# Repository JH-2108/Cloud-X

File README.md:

# Cloud-X
An educational model rocketry project exploring aerospace engineering, embedded programming and systems, electronics design and flight-data analysis

# Overview
This project explores the development of a model rocket and an accompanying STM32 based avionics data logging system. 

The electronics project focuses on collecting and recording sensor measurements, allowing data to be studied and visualized during engineering expreiments. 

# Objectives
- Explore aerospace engineering and model rocketry.
- Design a custom PCB using KiCAD
- Develop embedded firmware for an STM32 microcontroller
- Integrate motion and atmospheric pressure sensors
- Implement microSD data storage
- Analyze sensor measurements and visualize recorded data.
- Document the engineering and development process.

# Electronics
The avionics electronics design uses the following main components

|Component|Purpose|
|---|---|
|STM32F7SSRET6|Main microcontroller | 
| ICM-45686 | Motion sensin |
| BMP580 | Atmospheric pressure measurement | 
| HRS DM3D SF | microSD card interface | 
| USB type C | Programming and data transfer | 
| AP2112K-3.3 | Voltage regulation | 
| USBLC6-2SC6 | USB ESD protection | 

# PCB designing 
The custom PCB is designed using KiCAD 
The electronics documentation covers: 
- Schematic design
- PCB layout
- Component selection
- power-management review
- sensor integration
- firmware development
- design rule verification

# Firmware
Firmware development focuses on: 
- STM32 intialization
- Sensor communication
- Sensor data acquisition
- microSD data recording
- USB communication
- Diagnostic information

# Payload Ejection Plan
A motor engine would be used to propel the rocket upwards, upon hitting the apogee, the PCB would send out a tiny electrical signal to the e-matches, allowing the nose cone to release, the nose cone and the rest of the rocket body is connected through a shock cord, where the parachute would be opened closer to the nose cone instead, giving a large space for the flight controller to be released. This flight controller will  then measure altitude, atmospheric pressure, acceleration, and more, all of which is written onto an microSD card within the rocket flight controller itself. 

# Development tools 
- KiCAD: PCB and schematic design
- STM32CubeIDE: Embedded development
- OpenRocket software: Rocket designing 

# Safety 
This repository documents an educational aerospace engineering project. Any physical rocketry activities must follow applicable laws, recognized model rocketry safety standards and qualified adult supervision. 

The electronics documentation is **NOT** an instruction manual for constructing or operation propulsion or pyrotechnic systems. 

# BOM 
|Part                                                                                                                    |Type      |Quantity|Unit price (USD)|Line total (USD)|Link                                                                                                                                                                                                                                                                                                              |Vendor         |Funding|Notes                                                                      |
|------------------------------------------------------------------------------------------------------------------------|----------|--------|----------------|----------------|------------------------------------------------------------------------------------------------------------------------------------------------------------------------------------------------------------------------------------------------------------------------------------------------------------------|---------------|-------|---------------------------------------------------------------------------|
|STM32F722RET6                                                                                                           |Part      |1       |11.30           |11.30           |https://www.lcsc.com/product-detail/C118207.html?s_z=n_q_STM32F722RET6                                                                                                                                                                                                                                            |LCSC           |Grant  |Main microcontroller chip                                                  |
|ICM-45686                                                                                                               |Part      |1       |10.31           |10.31           |https://www.lcsc.com/product-detail/C22459454.html?s_z=n_q_ICM-45686                                                                                                                                                                                                                                              |LCSC           |Grant  |Motion sensor data acquisition                                             |
|BMP580                                                                                                                  |Part      |1       |1.21            |1.21            |https://www.lcsc.com/product-detail/C22391138.html?s_z=n_q_BMP580                                                                                                                                                                                                                                                 |LCSC           |Grant  |Atmospheric pressure measurement                                           |
|USB Type-C 16P SMT                                                                                                      |Part      |1       |0.60            |0.60            |https://www.lcsc.com/product-detail/USB-Connectors_hanxia-HX-TYPE-C-16P-SMT-J2-0_C42453849.html                                                                                                                                                                                                                   |LCSC           |Grant  |Programming and data transfer                                              |
|4.7kΩ resistor                                                                                                          |Part      |1       |0.32            |0.32            |https://www.lcsc.com/product-detail/C99782.html                                                                                                                                                                                                                                                                   |LCSC           |Grant  |I2C communication                                                          |
|ST USBLC6-2SC6                                                                                                          |Part      |1       |0.82            |0.82            |https://www.lcsc.com/product-detail/esd-and-surge-protection-tvs-esd_stmicroelectronics-usblc6-2sc6_C7519.html                                                                                                                                                                                                    |LCSC           |Grant  |ESD protection                                                             |
|SMD tactile push button, 4 pins                                                                                         |Part      |1       |0.50            |0.50            |https://www.lcsc.com/product-detail/C49234134.html?s_z=n_q_l_tactile%2520switch%2520SMD                                                                                                                                                                                                                           |LCSC           |Grant  |Reset and BOOT button                                                      |
|HONGLITRONIC PSC-1608U52GC-G4                                                                                           |Part      |1       |0.74            |0.74            |https://www.lcsc.com/product-detail/C22371297.html?s_z=n_q_0603%2520LED%2520green                                                                                                                                                                                                                                 |LCSC           |Grant  |Status LED                                                                 |
|Samsung Electro-Mechanics CL10B104KB8NNNC                                                                               |Part      |1       |0.72            |0.72            |https://www.lcsc.com/product-detail/C1591.html?s_z=n_q_t_100nf%25200603%2520capacitor                                                                                                                                                                                                                             |LCSC           |Grant  |Decoupling capacitors                                                      |
|Samsung Electro-Mechanics CL10A106KP8NNNC                                                                               |Part      |1       |0.41            |0.41            |https://www.lcsc.com/product-detail/C19702.html?s_z=n_q_t_10uF%25200603%2520capacitors                                                                                                                                                                                                                            |LCSC           |Grant  |Bulk capacitor                                                             |
|2.54mm, 1×04 pin header                                                                                                 |Part      |1       |1.03            |1.03            |https://shopee.com.my/Straight-Pin-Header-MALE-Single-Double-Row-2p-3p-4p-10p-40p-2.54mm-Pitch-i.678234279.17653071533?extraParams=%7B%22display_model_id%22%3A58675164377%2C%22model_selection_logic%22%3A2%7D&image_ids=my-11134207-7r990-ly9mj2d9bfqhc3                                                        |Shopee Malaysia|Grant  |debugging                                                                  |
|HRS DM3D-SF                                                                                                             |Part      |1       |1.60            |1.60            |https://www.lcsc.com/product-detail/C719027.html                                                                                                                                                                                                                                                                  |LCSC           |Grant  |MicroSD card holder                                                        |
|DIODES AP2112K-3.3TRG1                                                                                                  |Part      |1       |0.92            |0.92            |https://www.lcsc.com/product-detail/C51118.html?s_z=n_q_%2520C51118&globalKeyword=%2520C51118                                                                                                                                                                                                                     |LCSC           |Grant  |converts raw power input to save voltage level                             |
|DIODES B130-13-F                                                                                                        |Part      |1       |0.46            |0.46            |https://www.lcsc.com/product-detail/C134423.html                                                                                                                                                                                                                                                                  |LCSC           |Grant  |Protects the circuit if battery is placed incorrectly                      |
|UNI-ROYAL 0603WAF5101T5E                                                                                                |Part      |1       |0.16            |0.16            |https://www.lcsc.com/product-detail/C23186.html?s_z=n_q_C23186&globalKeyword=C23186                                                                                                                                                                                                                               |LCSC           |Grant  |tie CC1 and CC2 to GND                                                     |
|AOS AO3400A                                                                                                             |Part      |1       |0.45            |0.45            |https://www.lcsc.com/product-detail/C20917.html?s_z=n_q_C20917&globalKeyword=C20917                                                                                                                                                                                                                               |LCSC           |Grant  |Ignites parachutes when MCU detects apogee                                 |
|UNI-ROYAL 0603WAF1002T5E                                                                                                |Part      |1       |0.22            |0.22            |https://www.lcsc.com/product-detail/C25804.html?s_z=n_q_C25804&globalKeyword=C25804                                                                                                                                                                                                                               |LCSC           |Grant  |Manages boot configuration, ensures clean SD logging, and measures battery.|
|PCB manufacturing                                                                                                       |PCB       |1       |15.00           |15.00           |https://jlcpcb.com                                                                                                                                                                                                                                                                                                |jlcpcb         |Grant  |Rocket flight controller PCB manufacturing                                 |
|Print Legion                                                                                                            |3D printed|1       |30.00           |30.00           |https://printlegion.hackclub.com                                                                                                                                                                                                                                                                                  |print legion   |Grant  |Rocket body                                                                |
|GNB LiHV 2S 7.6V 1100mAh 60C XT30 LiPo Battery Long Range                                                               |Part      |1       |12.00           |12.00           |https://epicfpv.ca/products/gnb-lihv-2s-7-6v-1100mah-60c-xt30-lipo-battery-long-range-1?variant=60800320405790&country=MY&currency=MYR&utm_medium=product_sync&utm_source=google&utm_content=sag_organic&utm_campaign=sag_organic&srsltid=AYCX9vIx-3YrB9azhgDblcEGwU8ssDDiMy9BJdyDTWHyMrJqba1CQkDj8P8             |epicFPV        |Grant  |Battery for electronics and e-matches                                      |
|For Amass XT30PW Male For PCB Board Plug Banana Golden XT30 Connector Black 3.6mm 90 Degrees Right Angle XT30PW-M36 5NRT|Part      |1       |4.50            |4.50            |https://shopee.com.my/For-Amass-XT30PW-Male-For-PCB-Board-Plug-Banana-Golden-XT30-Connector-Black-3.6mm-90-Degrees-Right-Angle-XT30PW-M36-5NRT-i.348385455.53262738873?extraParams=%7B%22display_model_id%22%3A416107095660%2C%22model_selection_logic%22%3A3%7D&image_ids=sg-11134201-823p2-mp3yeoidr56oc4       |Shopee Malaysia|Grant  |Battery connector                                                          |
|Pyro screw terminals                                                                                                    |Part      |2       |1.00            |2.00            |https://shopee.com.my/2P-3P-4P-5P-6P-7P-8P-9P-10P-Pitch-2.54mm-3.81mm-5.00mm-5.08mm-Terminal-Block-Connector-PCB-DIY-Wire-Cable-KF128-i.90748406.20850140188?extraParams=%7B%22display_model_id%22%3A213007401440%2C%22model_selection_logic%22%3A3%7D&image_ids=my-11134207-7r98y-lwi43m3xsdwqa6                 |Shopee Malaysia|Grant  |Pyro e-matches ejector                                                     |
|E-matches for pyro system                                                                                               |Part      |1       |30.00           |30.00           |https://shopee.com.my/Electric-Ignitor-1m-2m-3m-E-Match-Talon-Firing-System-Rocket-Feux-D'artific-Fuse-Igniter-Pyrotechnic-i.251684114.26121992227?extraParams=%7B%22display_model_id%22%3A345451400630%2C%22model_selection_logic%22%3A3%7D&image_ids=my-11134207-7rase-m8e4x92ee8ms73                           |Shopee Malaysia|Grant  |E-matches for parachute system                                             |
|Heat resistant recovery wadding                                                                                         |Part      |1       |6.41            |6.41            |https://www.apogeerockets.com/Building-Supplies/Recovery-Equipment/Disposable-Wadding/Estes-Recovery-Wadding                                                                                                                                                                                                      |Estes          |Grant  |Protects the parachute fabric                                              |
|Parachute                                                                                                               |Part      |2       |10.00           |20.00           |https://estesrockets.com/products/rip-stop-parachute                                                                                                                                                                                                                                                              |Estes Rocket   |Grant  |Slow decent for the rocket                                                 |
|C6-0 Engines                                                                                                            |Part      |1       |15.00           |15.00           |https://estesrockets.com/products/c6-0-engines                                                                                                                                                                                                                                                                    |Estes Rocket   |Grant  |Rocket propulsion engine                                                   |
|3mm shock cords                                                                                                         |Part      |1       |0.35            |0.35            |https://shopee.com.my/1-1.5-2-.2.5-3-4-5mm-Length-2M-Black-Round-Elastic-Cord-Beading-Stretch-Thread-String-Rope-for-Necklace-Bracelet-Jewelry-Making-i.190957605.29855430851?extraParams=%7B%22display_model_id%22%3A139003971739%2C%22model_selection_logic%22%3A3%7D&image_ids=cn-11134207-7r98o-lxs0i2cxw8clb5|Shopee Malaysia|Grant  |Shock cords holding nose cone and rocket body                              |
|Total                                                                                                                   |          |        |                |167.03          |                                                                                                                                                                                                                                                                                                                  |               |       |                                                                           |

# Project pictures 

**Schematics**

**PCB**

**PCB 3D RENDERED**

**Avionics Bay**

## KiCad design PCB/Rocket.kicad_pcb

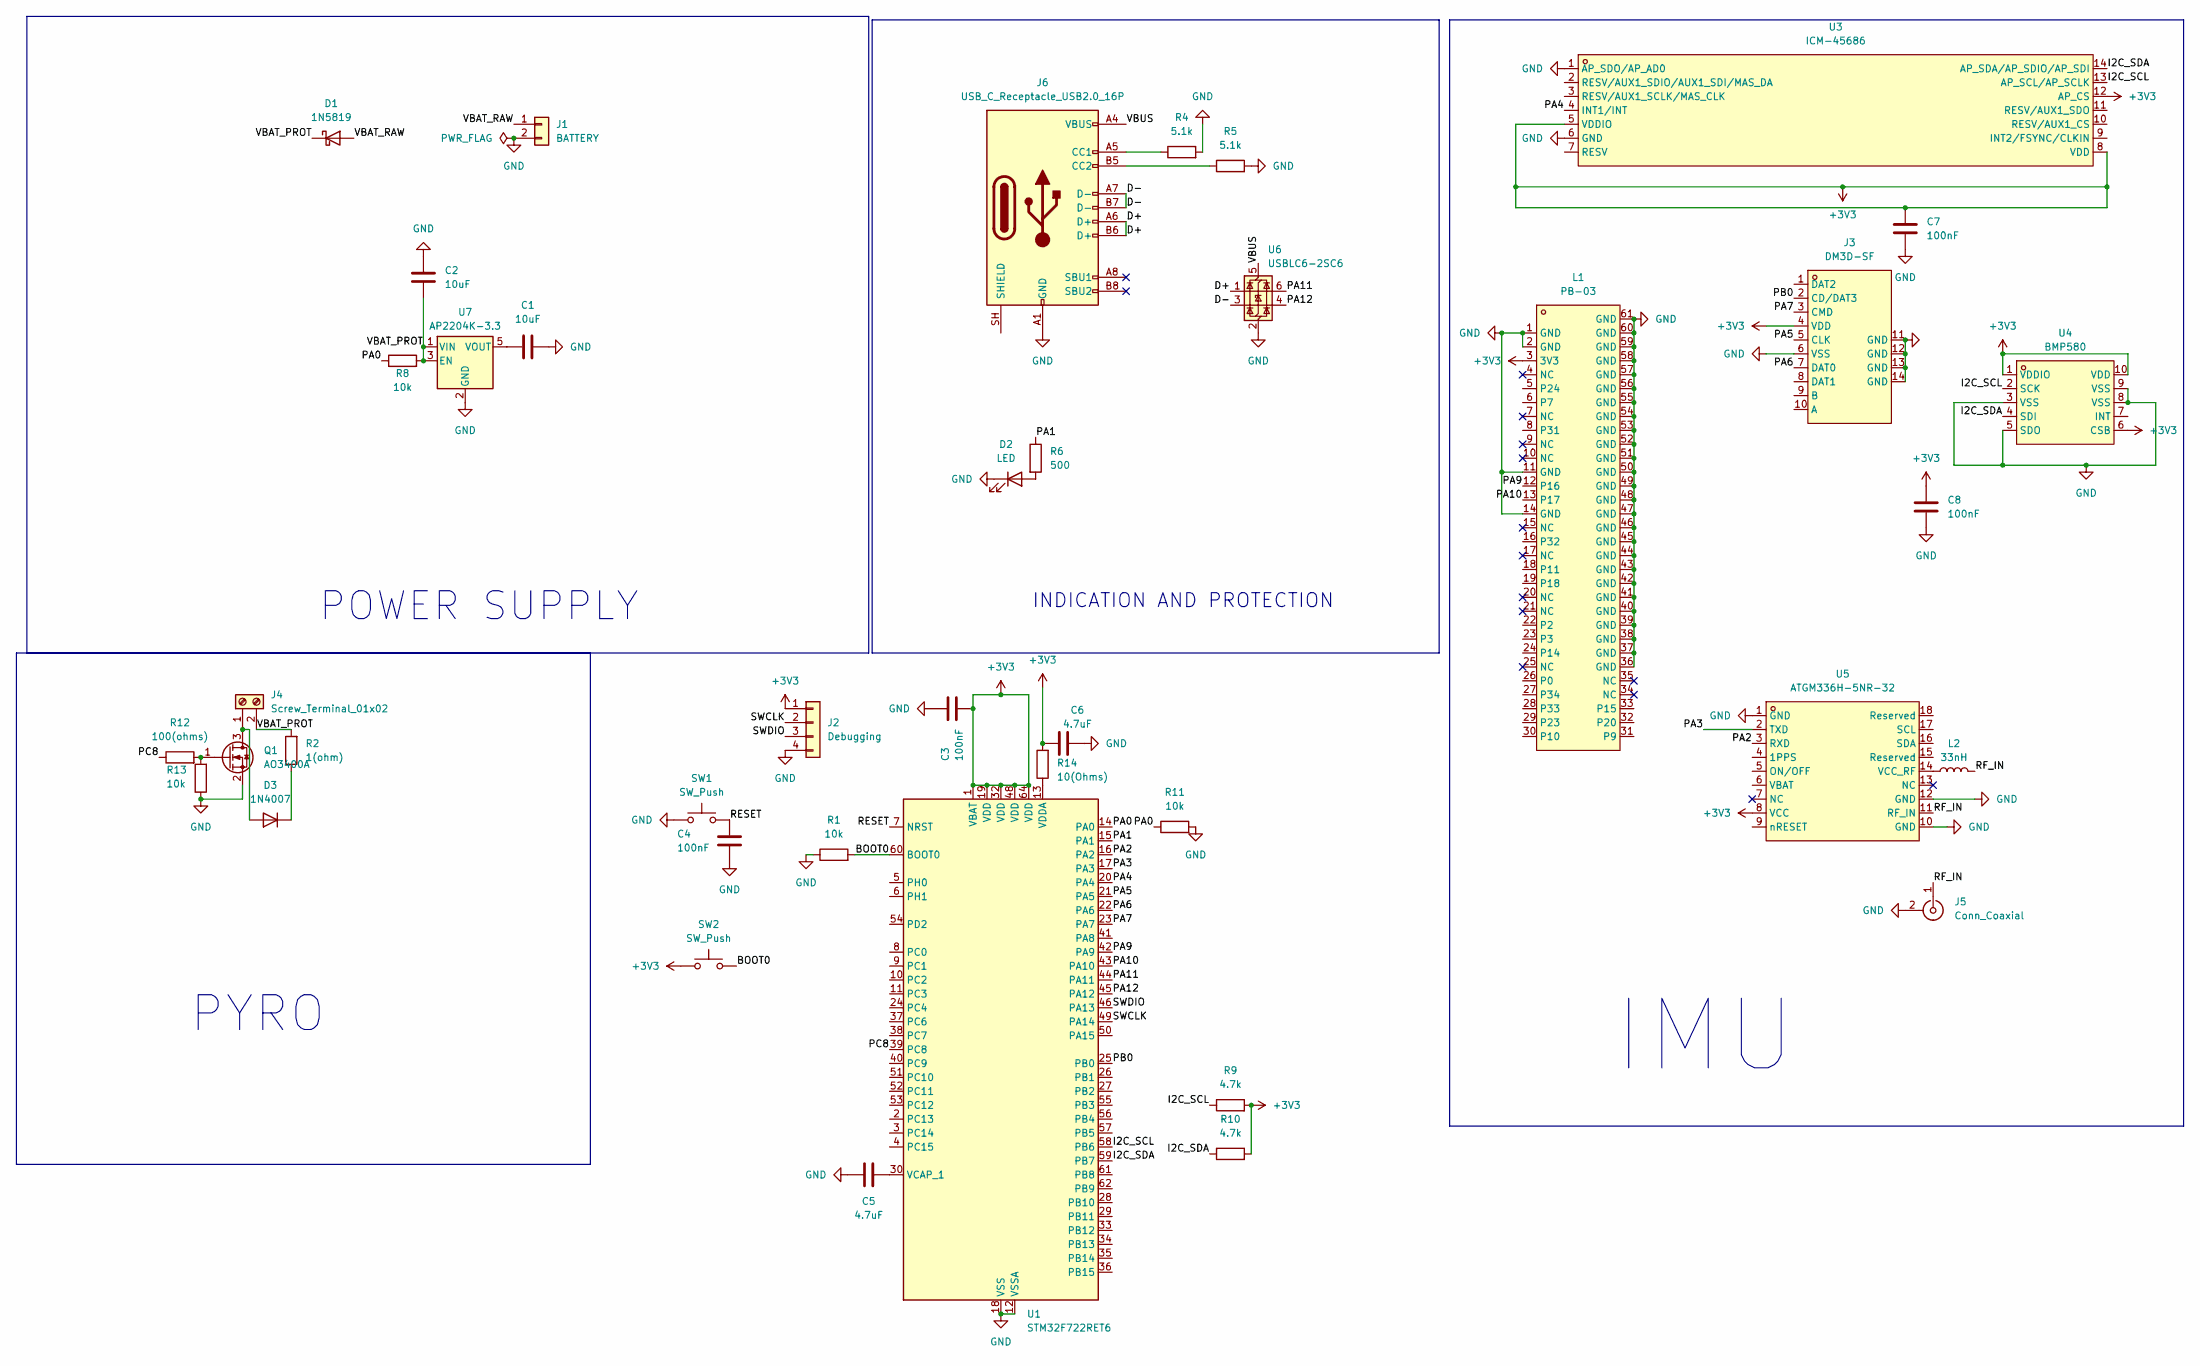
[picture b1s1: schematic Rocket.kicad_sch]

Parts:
C1, C2: 10uF; C_0603_1608Metric
C3, C4, C7, C8: 100nF; C_0603_1608Metric
C5, C6: 4.7uF; C_0603_1608Metric
D1: 1N5819; D_DO-41_SOD81_P10.16mm_Horizontal
D2: LED; LED_0603_1608Metric
D3: 1N4007; D_DO-41_SOD81_P10.16mm_Horizontal
J1: BATTERY; AMASS_XT30PW-M_1x02_P2.50mm_Horizontal
J2: Debugging; PinHeader_1x04_P2.54mm_Vertical
J3: DM3D-SF; TF-SMD_DM3D-SF; MPN DM3D-SF; LCSC Part C719027
J4: Screw_Terminal_01x02; TerminalBlock_Phoenix_MKDS-1,5-2-5.08_1x02_P5.08mm_Horizont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
J5: Conn_Coaxial; U.FL_Hirose_U.FL-R-SMT-1_Vertical
J6: USB_C_Receptacle_USB2.0_16P; USB_C_Receptacle_Palconn_UTC16-G
L1: PB-03; WIRELM-SMD_AI-THINKER_PB-03; MPN PB-03; LCSC Part C2980079
L2: 33nH; L_0603_1608Metric
Q1: AO3400A; SOT-23
R1, R8, R11, R13: 10k; R_0603_1608Metric
R2: 1(ohm); R_1206_3216Metric
R4, R5: 5.1k; R_0603_1608Metric
R6: 500; R_0603_1608Metric
R9, R10: 4.7k; R_0603_1608Metric
R12: 100(ohms); R_0603_1608Metric
R14: 10(Ohms); R_0603_1608Metric
SW1, SW2: SW_Push; SW-SMD_4P-L5.2-W5.2-P3.70-LS6.4
U1: STM32F722RET6; LQFP-64_10x10mm_P0.5mm
U3: ICM-45686; LGA-14_L3.0-W2.5-P0.50-TL; MPN ICM-45686; LCSC Part C22459454
U4: BMP580; LGA-10_L2.0-W2.0-P0.50-TL_BMP580; MPN BMP580; LCSC Part C22391138
U5: ATGM336H-5NR-32; GPS-SMD_18P-L10.1-W9.7-P1.10-TL; MPN ATGM336H-5NR32; LCSC Part C5117921
U6: USBLC6-2SC6; SOT-23-6
U7: AP2204K-3.3; SOT-23-5

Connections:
+3V3: C3.1, C6.1, C7.1, C8.1, J2.1, J3.4 (VDD), L1.3 (3V3), R9.2, R10.2, R14.2, SW2.1, U1.1 (VBAT), U1.19 (VDD), U1.32 (VDD), U1.48 (VDD), U1.64 (VDD), U3.5 (VDDIO), U3.8 (VDD), U3.12 (AP_CS), U4.1 (VDDIO), U4.6 (CSB), U4.10 (VDD), U5.8 (VCC)
/BOOT0: R1.2, SW2.2, U1.60 (BOOT0)
/D+: J6.A6 (D+), J6.B6 (D+), U6.1 (I/O1)
/D-: J6.A7 (D-), J6.B7 (D-), U6.3 (I/O2)
/I2C_SCL: R9.1, U1.58 (PB6), U3.13 (AP_SCL/AP_SCLK), U4.2 (SCK)
/I2C_SDA: R10.1, U1.59 (PB7), U3.14 (AP_SDA/AP_SDIO/AP_SDI), U4.4 (SDI)
/PA0: R8.1, R11.1, U1.14 (PA0)
/PA1: R6.1, U1.15 (PA1)
/PA2: U1.16 (PA2), U5.3 (RXD)
/PA3: U1.17 (PA3), U5.2 (TXD)
/PA4: U1.20 (PA4), U3.4 (INT1/INT)
/PA5: J3.5 (CLK), U1.21 (PA5)
/PA6: J3.7 (DAT0), U1.22 (PA6)
/PA7: J3.3 (CMD), U1.23 (PA7)
/PA9: L1.12 (P16), U1.42 (PA9)
/PA10: L1.13 (P17), U1.43 (PA10)
/PA11: U1.44 (PA11), U6.6 (I/O1)
/PA12: U1.45 (PA12), U6.4 (I/O2)
/PB0: J3.2 (CD/DAT3), U1.25 (PB0)
/PC8: R12.1, U1.39 (PC8)
/RESET: C4.2, SW1.2, U1.7 (NRST)
/RF_IN: J5.1 (In), L2.2, U5.11 (RF_IN)
/SWCLK: J2.2, U1.49 (PA14)
/SWDIO: J2.3, U1.46 (PA13)
/VBAT_PROT: C2.2, D1.1 (K), J4.2, R2.2, R8.2, U7.1 (VIN), U7.3 (EN)
/VBAT_RAW: D1.2 (A), J1.1
/VBUS: J6.A4 (VBUS), J6.A9 (VBUS), J6.B4 (VBUS), J6.B9 (VBUS), U6.5 (VBUS)
GND: C1.2, C2.1, C3.2, C4.1, C5.1, C6.2, C7.2, C8.2, D2.1 (K), J1.2, J2.4, J3.6 (VSS), J3.11 (GND), J3.12 (GND), J3.13 (GND), J3.14 (GND), J5.2 (Ext), J6.A1 (GND), J6.A12 (GND), J6.B1 (GND), J6.B12 (GND), L1.1 (GND), L1.2 (GND), L1.11 (GND), L1.14 (GND), L1.36 (GND), L1.37 (GND), L1.38 (GND), L1.39 (GND), L1.40 (GND), L1.41 (GND), L1.42 (GND), L1.43 (GND), L1.44 (GND), L1.45 (GND), L1.46 (GND), L1.47 (GND), L1.48 (GND), L1.49 (GND), L1.50 (GND), L1.51 (GND), L1.52 (GND), L1.53 (GND), L1.54 (GND), L1.55 (GND), L1.56 (GND), L1.57 (GND), L1.58 (GND), L1.59 (GND), L1.60 (GND), L1.61 (GND), Q1.2 (S), R1.1, R4.2, R5.2, R11.2, R13.1, SW1.1, U1.12 (VSSA), U1.18 (VSS), U1.31 (VSS), U1.47 (VSS), U1.63 (VSS), U3.1 (AP_SDO/AP_AD0), U3.6 (GND), U4.3 (VSS), U4.5 (SDO), U4.8 (VSS), U4.9 (VSS), U5.1 (GND), U5.10 (GND), U5.12 (GND), U6.2 (GND), U7.2 (GND)
unnamed: D2.2 (A), R6.2
unnamed: D3.2 (A), J4.1, Q1.3 (D)
unnamed: D3.1 (K), R2.1
unnamed: J6.A5 (CC1), R4.1
unnamed: J6.B5 (CC2), R5.1
unnamed: Q1.1 (G), R12.2, R13.2
unnamed: C5.2, U1.30 (VCAP_1)
unnamed: R14.1, U1.13 (VDDA)
unnamed: L2.1, U5.14 (VCC_RF)
unnamed: C1.1, U7.5 (VOUT)

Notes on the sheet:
POWER SUPPLY
PYRO
IMU
INDICATION AND PROTECTION

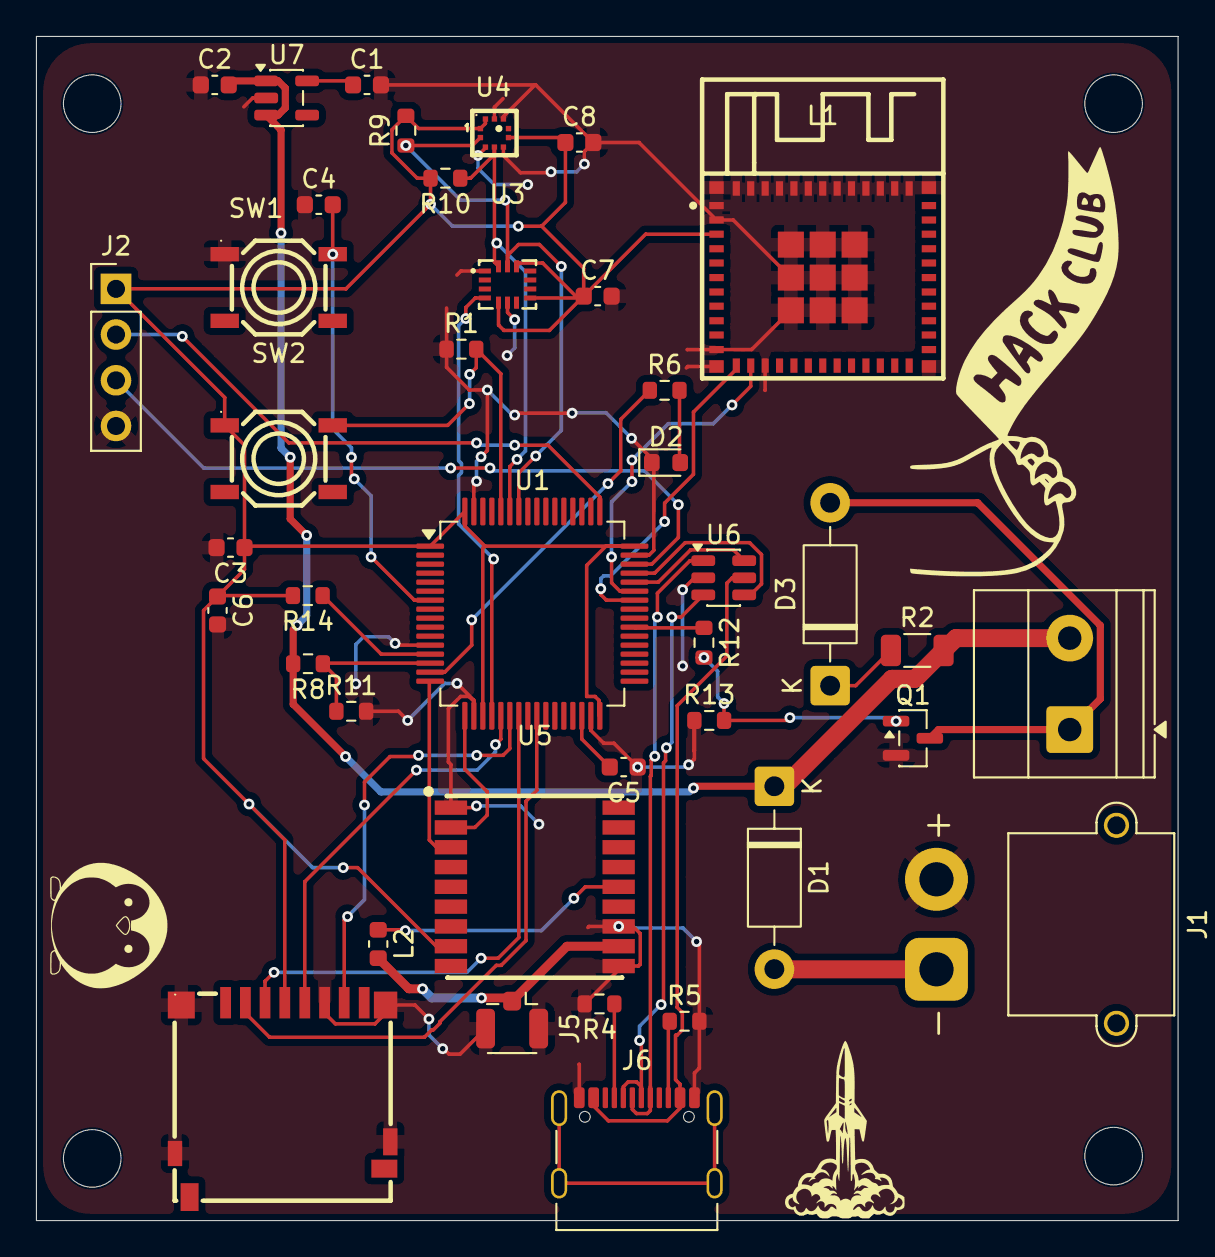
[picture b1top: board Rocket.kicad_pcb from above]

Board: 2 copper layers, 63.4 x 65.8 mm, 40 parts (0 on the bottom side), 38 nets.
